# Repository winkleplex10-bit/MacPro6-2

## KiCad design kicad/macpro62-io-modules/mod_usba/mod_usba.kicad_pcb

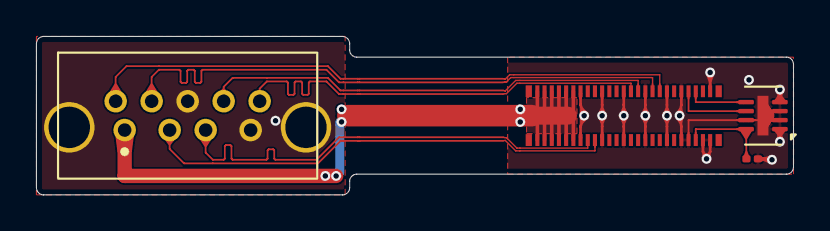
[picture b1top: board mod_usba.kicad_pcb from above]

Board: 2 copper layers, 42.1 x 8.8 mm, 4 parts (0 on the bottom side), 11 nets.

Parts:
C1: 100nF 0201 X5R 10V (3V3_MOD); C_0201_0603Metric
J1: MOD-A - Hong Cheng HC-USB3.0-L137-WJ (C7501870) T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; MP62_MOD_USB_A3_HC-USB3.0-L137-WJ
J2: DF40C-50DP-0.4V(51) C424645 -> JMn DF40C-50DS (PM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; MP62_Hirose_DF40C-50DP-0.4V
U1: BL24C02F-NTRC (C2828222) 24C02 ID EEPROM @0x50; DFN-8-1EP_2x3mm_P0.5mm_EP0.61x2.2mm

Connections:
3V3_MOD: C1.1, J2.46, U1.8
D_N: J1.2, J2.18
D_P: J1.3, J2.16
GND: C1.2, J1.4, J1.7, J1.S, J2.13, J2.14, J2.19, J2.20, J2.25, J2.26, J2.31, J2.32, J2.37, J2.38, J2.41, J2.42, J2.44, J2.48, J2.49, J2.50, U1.1, U1.2, U1.3, U1.4, U1.7, U1.9
ID_SCL: J2.43, U1.6
ID_SDA: J2.45, U1.5
SSRX_N: J1.5, J2.27
SSRX_P: J1.6, J2.29
SSTX_N: J1.8, J2.33
SSTX_P: J1.9, J2.35
VBUS: J1.1, J2.1, J2.2, J2.3, J2.4, J2.5, J2.6, J2.7, J2.8, J2.9, J2.10, J2.11, J2.12

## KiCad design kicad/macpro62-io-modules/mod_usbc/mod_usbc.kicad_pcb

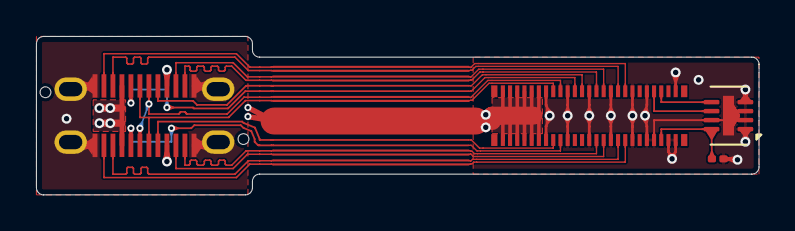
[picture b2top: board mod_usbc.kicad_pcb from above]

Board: 2 copper layers, 40.1 x 8.8 mm, 4 parts (0 on the bottom side), 19 nets.

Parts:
C1: 100nF 0201 X5R 10V (3V3_MOD); C_0201_0603Metric
J1: MOD-C - HOAUC HYCW417-USBC24-180B (C5342202) SMD 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; HOAUC_HYCW417-USBC24-180B
J2: DF40C-50DP-0.4V(51) C424645 -> JMn DF40C-50DS (PM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; MP62_Hirose_DF40C-50DP-0.4V
U1: BL24C02F-NTRC (C2828222) 24C02 ID EEPROM @0x50; DFN-8-1EP_2x3mm_P0.5mm_EP0.61x2.2mm

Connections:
3V3_MOD: C1.1, J2.46, U1.8
CC1: J1.A5, J2.21
CC2: J1.B5, J2.16
D_N: J1.A7, J1.B7, J2.17
D_P: J1.A6, J1.B6, J2.15
GND: C1.2, J1.A1, J1.A12, J1.B1, J1.B12, J1.S, J2.13, J2.14, J2.19, J2.20, J2.25, J2.26, J2.31, J2.32, J2.37, J2.38, J2.41, J2.42, J2.44, J2.48, J2.49, J2.50, U1.1, U1.2, U1.3, U1.4, U1.7, U1.9
ID_SCL: J2.43, U1.6
ID_SDA: J2.45, U1.5
SBU1: J1.A8, J2.23
SBU2: J1.B8, J2.18
SSRX1_N: J1.B10, J2.34
SSRX1_P: J1.B11, J2.36
SSRX2_N: J1.A10, J2.29
SSRX2_P: J1.A11, J2.27
SSTX1_N: J1.A3, J2.33
SSTX1_P: J1.A2, J2.35
SSTX2_N: J1.B3, J2.30
SSTX2_P: J1.B2, J2.28
VBUS: J1.A4, J1.A9, J1.B4, J1.B9, J2.1, J2.2, J2.3, J2.4, J2.5, J2.6, J2.7, J2.8, J2.9, J2.10, J2.11, J2.12

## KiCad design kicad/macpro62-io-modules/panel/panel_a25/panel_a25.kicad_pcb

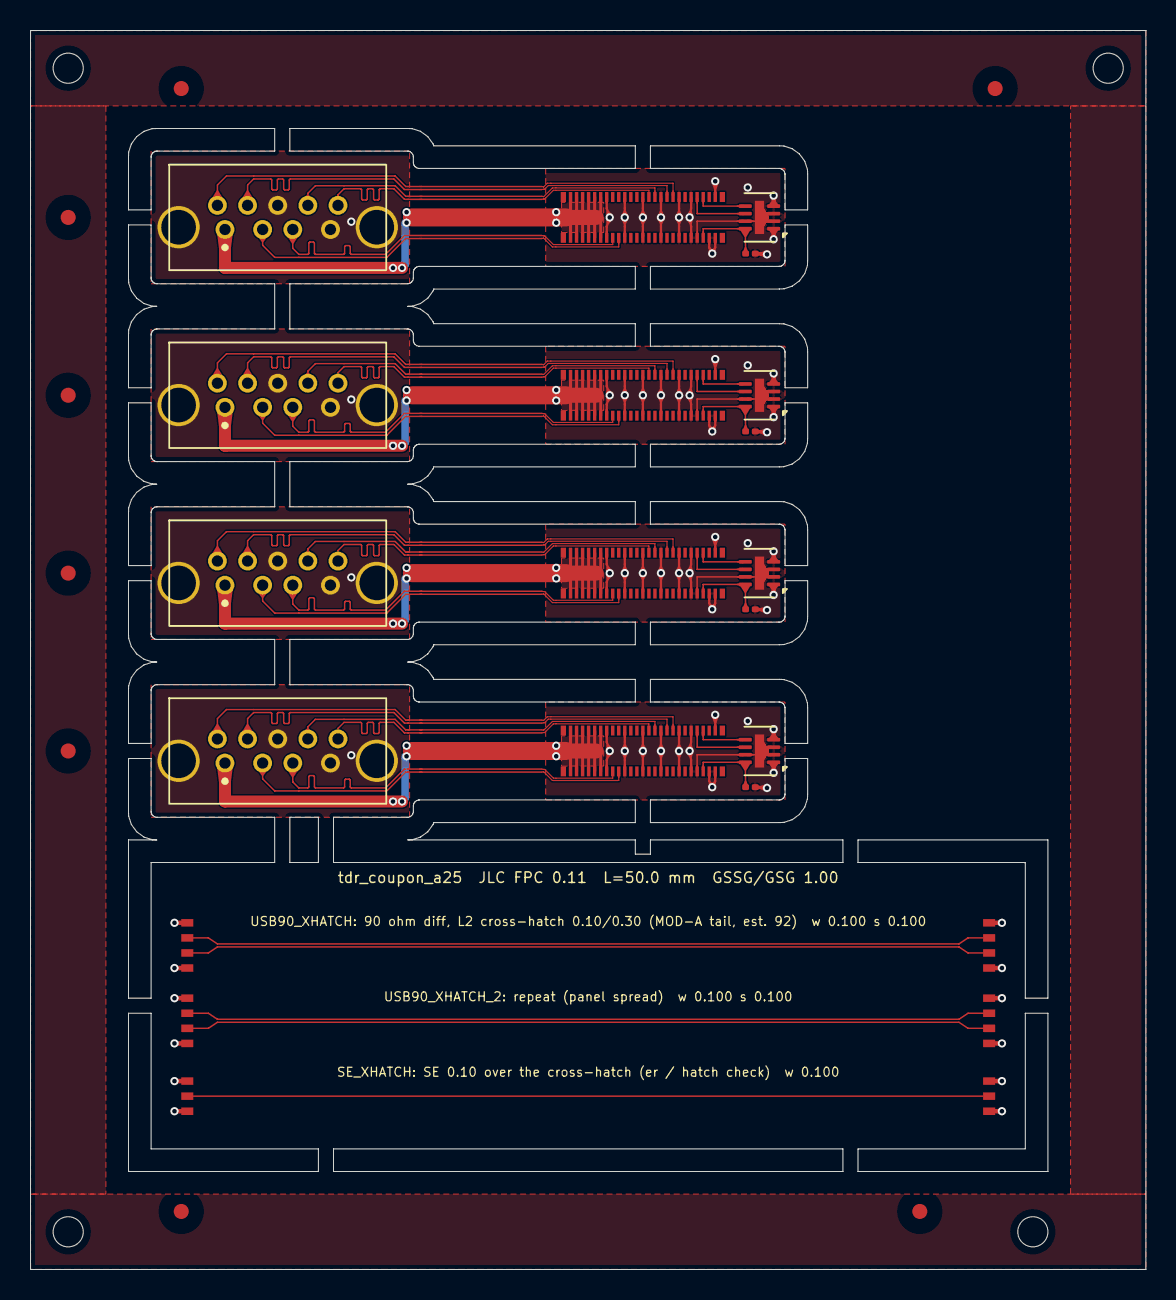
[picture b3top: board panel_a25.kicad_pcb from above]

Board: 2 copper layers, 74.0 x 82.2 mm, 34 parts (0 on the bottom side), 50 nets.

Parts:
C1_A1, C1_A2, C1_A3, C1_A4: 100nF 0201 X5R 10V (3V3_MOD); C_0201_0603Metric
FID1, FID2, FID3, FID4, FID5, FID6, FID7, FID8: Fiducial_1mm_Mask2mm
J1_A1, J1_A2, J1_A3, J1_A4: MOD-A - Hong Cheng HC-USB3.0-L137-WJ (C7501870) T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; MP62_MOD_USB_A3_HC-USB3.0-L137-WJ
J2_A1, J2_A2, J2_A3, J2_A4: DF40C-50DP-0.4V(51) C424645 -> JMn DF40C-50DS (PM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; MP62_Hirose_DF40C-50DP-0.4V
TH1, TH2, TH3, TH4: TOOLING_2.0
TP1A_T, TP1B_T, TP2A_T, TP2B_T, TP3A_T, TP3B_T: TDR_LAUNCH
U1_A1, U1_A2, U1_A3, U1_A4: BL24C02F-NTRC (C2828222) 24C02 ID EEPROM @0x50; DFN-8-1EP_2x3mm_P0.5mm_EP0.61x2.2mm

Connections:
A1/3V3_MOD: C1_A1.1, J2_A1.46, U1_A1.8
A1/D_N: J1_A1.2, J2_A1.18
A1/D_P: J1_A1.3, J2_A1.16
A1/GND: C1_A1.2, J1_A1.4, J1_A1.7, J1_A1.S, J2_A1.13, J2_A1.14, J2_A1.19, J2_A1.20, J2_A1.25, J2_A1.26, J2_A1.31, J2_A1.32, J2_A1.37, J2_A1.38, J2_A1.41, J2_A1.42, J2_A1.44, J2_A1.48, J2_A1.49, J2_A1.50, U1_A1.1, U1_A1.2, U1_A1.3, U1_A1.4, U1_A1.7, U1_A1.9
A1/ID_SCL: J2_A1.43, U1_A1.6
A1/ID_SDA: J2_A1.45, U1_A1.5
A1/SSRX_N: J1_A1.5, J2_A1.27
A1/SSRX_P: J1_A1.6, J2_A1.29
A1/SSTX_N: J1_A1.8, J2_A1.33
A1/SSTX_P: J1_A1.9, J2_A1.35
A1/VBUS: J1_A1.1, J2_A1.1, J2_A1.2, J2_A1.3, J2_A1.4, J2_A1.5, J2_A1.6, J2_A1.7, J2_A1.8, J2_A1.9, J2_A1.10, J2_A1.11, J2_A1.12
A2/3V3_MOD: C1_A2.1, J2_A2.46, U1_A2.8
A2/D_N: J1_A2.2, J2_A2.18
A2/D_P: J1_A2.3, J2_A2.16
A2/GND: C1_A2.2, J1_A2.4, J1_A2.7, J1_A2.S, J2_A2.13, J2_A2.14, J2_A2.19, J2_A2.20, J2_A2.25, J2_A2.26, J2_A2.31, J2_A2.32, J2_A2.37, J2_A2.38, J2_A2.41, J2_A2.42, J2_A2.44, J2_A2.48, J2_A2.49, J2_A2.50, U1_A2.1, U1_A2.2, U1_A2.3, U1_A2.4, U1_A2.7, U1_A2.9
A2/ID_SCL: J2_A2.43, U1_A2.6
A2/ID_SDA: J2_A2.45, U1_A2.5
A2/SSRX_N: J1_A2.5, J2_A2.27
A2/SSRX_P: J1_A2.6, J2_A2.29
A2/SSTX_N: J1_A2.8, J2_A2.33
A2/SSTX_P: J1_A2.9, J2_A2.35
A2/VBUS: J1_A2.1, J2_A2.1, J2_A2.2, J2_A2.3, J2_A2.4, J2_A2.5, J2_A2.6, J2_A2.7, J2_A2.8, J2_A2.9, J2_A2.10, J2_A2.11, J2_A2.12
A3/3V3_MOD: C1_A3.1, J2_A3.46, U1_A3.8
A3/D_N: J1_A3.2, J2_A3.18
A3/D_P: J1_A3.3, J2_A3.16
A3/GND: C1_A3.2, J1_A3.4, J1_A3.7, J1_A3.S, J2_A3.13, J2_A3.14, J2_A3.19, J2_A3.20, J2_A3.25, J2_A3.26, J2_A3.31, J2_A3.32, J2_A3.37, J2_A3.38, J2_A3.41, J2_A3.42, J2_A3.44, J2_A3.48, J2_A3.49, J2_A3.50, U1_A3.1, U1_A3.2, U1_A3.3, U1_A3.4, U1_A3.7, U1_A3.9
A3/ID_SCL: J2_A3.43, U1_A3.6
A3/ID_SDA: J2_A3.45, U1_A3.5
A3/SSRX_N: J1_A3.5, J2_A3.27
A3/SSRX_P: J1_A3.6, J2_A3.29
A3/SSTX_N: J1_A3.8, J2_A3.33
A3/SSTX_P: J1_A3.9, J2_A3.35
A3/VBUS: J1_A3.1, J2_A3.1, J2_A3.2, J2_A3.3, J2_A3.4, J2_A3.5, J2_A3.6, J2_A3.7, J2_A3.8, J2_A3.9, J2_A3.10, J2_A3.11, J2_A3.12
A4/3V3_MOD: C1_A4.1, J2_A4.46, U1_A4.8
A4/D_N: J1_A4.2, J2_A4.18
A4/D_P: J1_A4.3, J2_A4.16
A4/GND: C1_A4.2, J1_A4.4, J1_A4.7, J1_A4.S, J2_A4.13, J2_A4.14, J2_A4.19, J2_A4.20, J2_A4.25, J2_A4.26, J2_A4.31, J2_A4.32, J2_A4.37, J2_A4.38, J2_A4.41, J2_A4.42, J2_A4.44, J2_A4.48, J2_A4.49, J2_A4.50, U1_A4.1, U1_A4.2, U1_A4.3, U1_A4.4, U1_A4.7, U1_A4.9
A4/ID_SCL: J2_A4.43, U1_A4.6
A4/ID_SDA: J2_A4.45, U1_A4.5
A4/SSRX_N: J1_A4.5, J2_A4.27
A4/SSRX_P: J1_A4.6, J2_A4.29
A4/SSTX_N: J1_A4.8, J2_A4.33
A4/SSTX_P: J1_A4.9, J2_A4.35
A4/VBUS: J1_A4.1, J2_A4.1, J2_A4.2, J2_A4.3, J2_A4.4, J2_A4.5, J2_A4.6, J2_A4.7, J2_A4.8, J2_A4.9, J2_A4.10, J2_A4.11, J2_A4.12
T/GND: TP1A_T.1, TP1A_T.4, TP1B_T.1, TP1B_T.4, TP2A_T.1, TP2A_T.4, TP2B_T.1, TP2B_T.4, TP3A_T.1, TP3A_T.3, TP3B_T.1, TP3B_T.3
T/SE_XHATCH: TP3A_T.2, TP3B_T.2
T/USB90_XHATCH_2_N: TP2A_T.3, TP2B_T.3
T/USB90_XHATCH_2_P: TP2A_T.2, TP2B_T.2
T/USB90_XHATCH_N: TP1A_T.3, TP1B_T.3
T/USB90_XHATCH_P: TP1A_T.2, TP1B_T.2

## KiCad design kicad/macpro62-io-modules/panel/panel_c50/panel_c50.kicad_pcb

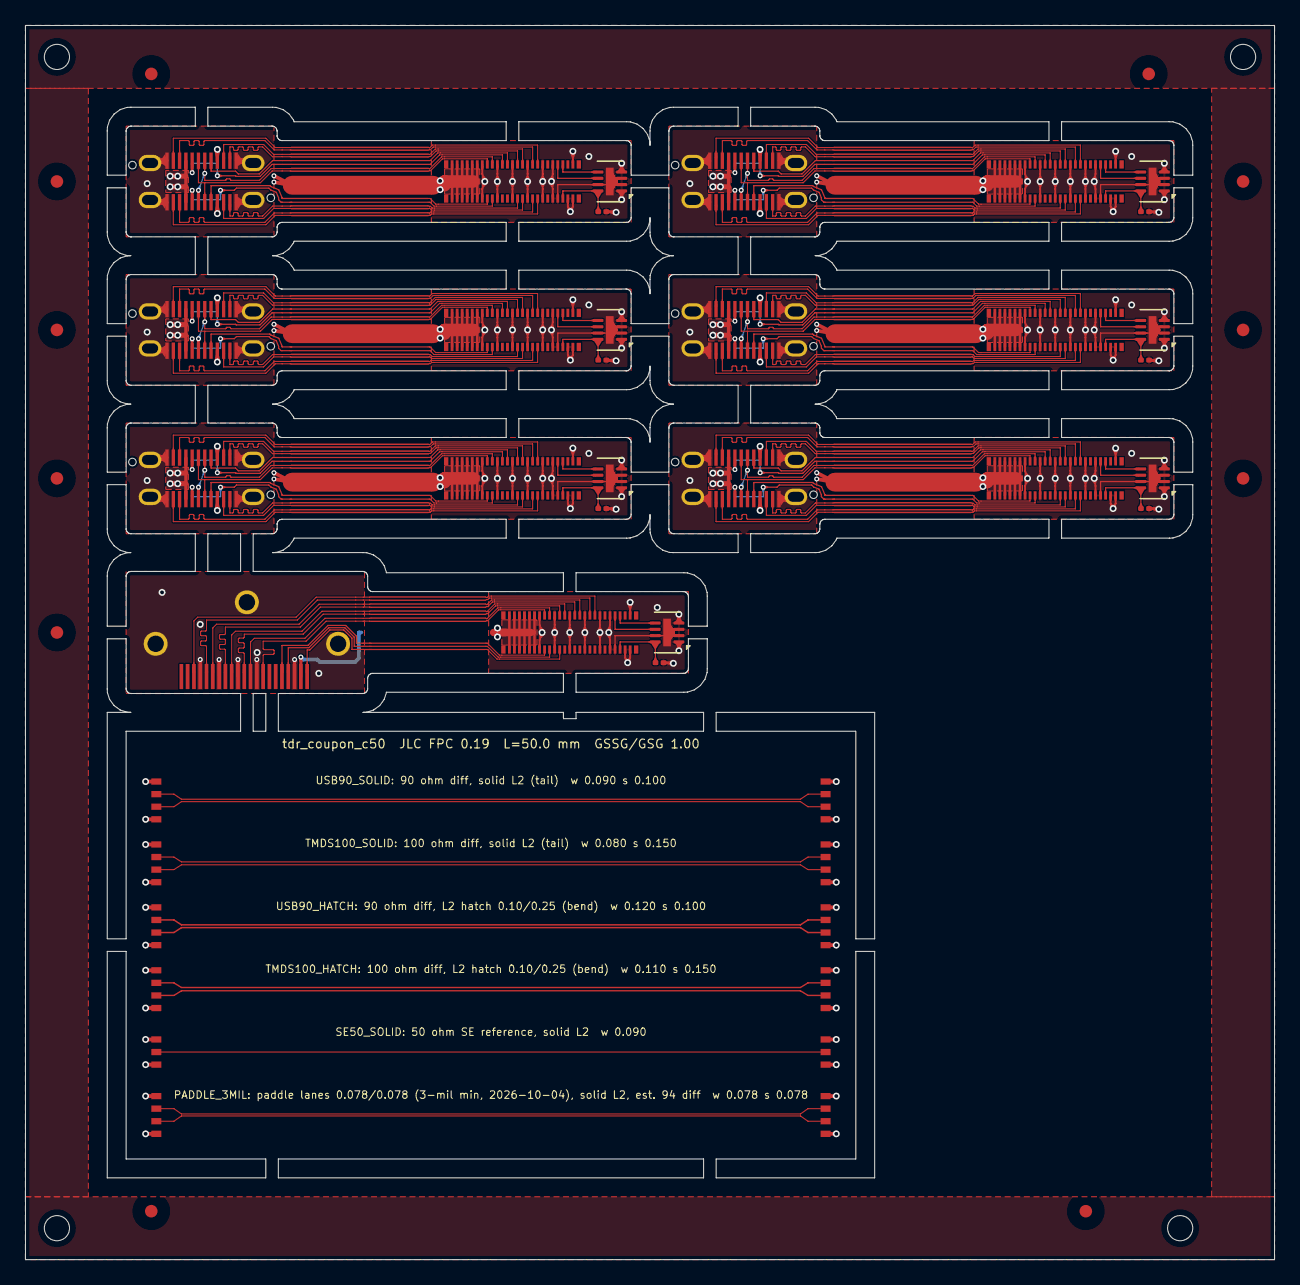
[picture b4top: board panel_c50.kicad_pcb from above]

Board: 2 copper layers, 99.3 x 98.1 mm, 55 parts (0 on the bottom side), 142 nets.

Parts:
C1_C1, C1_C2, C1_C3, C1_C4, C1_C5, C1_C6, C1_H: 100nF 0201 X5R 10V (3V3_MOD); C_0201_0603Metric
FID1, FID2, FID3, FID4, FID5, FID6, FID7, FID8, FID9, FID10, FID11: Fiducial_1mm_Mask2mm
J1_C1, J1_C2, J1_C3, J1_C4, J1_C5, J1_C6: MOD-C - HOAUC HYCW417-USBC24-180B (C5342202) SMD 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; HOAUC_HYCW417-USBC24-180B
J1_H: MOD-H - HOAUC HYC79-HDMIA19-105 (C711353) 19 SMD 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; HOAUC_HYC79-HDMIA19-105
J2_C1, J2_C2, J2_C3, J2_C4, J2_C5, J2_C6, J2_H: DF40C-50DP-0.4V(51) C424645 -> JMn DF40C-50DS (PM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; MP62_Hirose_DF40C-50DP-0.4V
TH1, TH2, TH3, TH4: TOOLING_2.0
TP1A_T, TP1B_T, TP2A_T, TP2B_T, TP3A_T, TP3B_T, TP4A_T, TP4B_T, TP5A_T, TP5B_T, TP6A_T, TP6B_T: TDR_LAUNCH
U1_C1, U1_C2, U1_C3, U1_C4, U1_C5, U1_C6, U1_H: BL24C02F-NTRC (C2828222) 24C02 ID EEPROM @0x50; DFN-8-1EP_2x3mm_P0.5mm_EP0.61x2.2mm

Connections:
C1/3V3_MOD: C1_C1.1, J2_C1.46, U1_C1.8
C1/CC1: J1_C1.A5, J2_C1.21
C1/CC2: J1_C1.B5, J2_C1.16
C1/D_N: J1_C1.A7, J1_C1.B7, J2_C1.17
C1/D_P: J1_C1.A6, J1_C1.B6, J2_C1.15
C1/GND: C1_C1.2, J1_C1.A1, J1_C1.A12, J1_C1.B1, J1_C1.B12, J1_C1.S, J2_C1.13, J2_C1.14, J2_C1.19, J2_C1.20, J2_C1.25, J2_C1.26, J2_C1.31, J2_C1.32, J2_C1.37, J2_C1.38, J2_C1.41, J2_C1.42, J2_C1.44, J2_C1.48, J2_C1.49, J2_C1.50, U1_C1.1, U1_C1.2, U1_C1.3, U1_C1.4, U1_C1.7, U1_C1.9
C1/ID_SCL: J2_C1.43, U1_C1.6
C1/ID_SDA: J2_C1.45, U1_C1.5
C1/SBU1: J1_C1.A8, J2_C1.23
C1/SBU2: J1_C1.B8, J2_C1.18
C1/SSRX1_N: J1_C1.B10, J2_C1.34
C1/SSRX1_P: J1_C1.B11, J2_C1.36
C1/SSRX2_N: J1_C1.A10, J2_C1.29
C1/SSRX2_P: J1_C1.A11, J2_C1.27
C1/SSTX1_N: J1_C1.A3, J2_C1.33
C1/SSTX1_P: J1_C1.A2, J2_C1.35
C1/SSTX2_N: J1_C1.B3, J2_C1.30
C1/SSTX2_P: J1_C1.B2, J2_C1.28
C1/VBUS: J1_C1.A4, J1_C1.A9, J1_C1.B4, J1_C1.B9, J2_C1.1, J2_C1.2, J2_C1.3, J2_C1.4, J2_C1.5, J2_C1.6, J2_C1.7, J2_C1.8, J2_C1.9, J2_C1.10, J2_C1.11, J2_C1.12
C2/3V3_MOD: C1_C2.1, J2_C2.46, U1_C2.8
C2/CC1: J1_C2.A5, J2_C2.21
C2/CC2: J1_C2.B5, J2_C2.16
C2/D_N: J1_C2.A7, J1_C2.B7, J2_C2.17
C2/D_P: J1_C2.A6, J1_C2.B6, J2_C2.15
C2/GND: C1_C2.2, J1_C2.A1, J1_C2.A12, J1_C2.B1, J1_C2.B12, J1_C2.S, J2_C2.13, J2_C2.14, J2_C2.19, J2_C2.20, J2_C2.25, J2_C2.26, J2_C2.31, J2_C2.32, J2_C2.37, J2_C2.38, J2_C2.41, J2_C2.42, J2_C2.44, J2_C2.48, J2_C2.49, J2_C2.50, U1_C2.1, U1_C2.2, U1_C2.3, U1_C2.4, U1_C2.7, U1_C2.9
C2/ID_SCL: J2_C2.43, U1_C2.6
C2/ID_SDA: J2_C2.45, U1_C2.5
C2/SBU1: J1_C2.A8, J2_C2.23
C2/SBU2: J1_C2.B8, J2_C2.18
C2/SSRX1_N: J1_C2.B10, J2_C2.34
C2/SSRX1_P: J1_C2.B11, J2_C2.36
C2/SSRX2_N: J1_C2.A10, J2_C2.29
C2/SSRX2_P: J1_C2.A11, J2_C2.27
C2/SSTX1_N: J1_C2.A3, J2_C2.33
C2/SSTX1_P: J1_C2.A2, J2_C2.35
C2/SSTX2_N: J1_C2.B3, J2_C2.30
C2/SSTX2_P: J1_C2.B2, J2_C2.28
C2/VBUS: J1_C2.A4, J1_C2.A9, J1_C2.B4, J1_C2.B9, J2_C2.1, J2_C2.2, J2_C2.3, J2_C2.4, J2_C2.5, J2_C2.6, J2_C2.7, J2_C2.8, J2_C2.9, J2_C2.10, J2_C2.11, J2_C2.12
C3/3V3_MOD: C1_C3.1, J2_C3.46, U1_C3.8
C3/CC1: J1_C3.A5, J2_C3.21
C3/CC2: J1_C3.B5, J2_C3.16
C3/D_N: J1_C3.A7, J1_C3.B7, J2_C3.17
C3/D_P: J1_C3.A6, J1_C3.B6, J2_C3.15
C3/GND: C1_C3.2, J1_C3.A1, J1_C3.A12, J1_C3.B1, J1_C3.B12, J1_C3.S, J2_C3.13, J2_C3.14, J2_C3.19, J2_C3.20, J2_C3.25, J2_C3.26, J2_C3.31, J2_C3.32, J2_C3.37, J2_C3.38, J2_C3.41, J2_C3.42, J2_C3.44, J2_C3.48, J2_C3.49, J2_C3.50, U1_C3.1, U1_C3.2, U1_C3.3, U1_C3.4, U1_C3.7, U1_C3.9
C3/ID_SCL: J2_C3.43, U1_C3.6
C3/ID_SDA: J2_C3.45, U1_C3.5
C3/SBU1: J1_C3.A8, J2_C3.23
C3/SBU2: J1_C3.B8, J2_C3.18
C3/SSRX1_N: J1_C3.B10, J2_C3.34
C3/SSRX1_P: J1_C3.B11, J2_C3.36
C3/SSRX2_N: J1_C3.A10, J2_C3.29
C3/SSRX2_P: J1_C3.A11, J2_C3.27
C3/SSTX1_N: J1_C3.A3, J2_C3.33
C3/SSTX1_P: J1_C3.A2, J2_C3.35
C3/SSTX2_N: J1_C3.B3, J2_C3.30
C3/SSTX2_P: J1_C3.B2, J2_C3.28
C3/VBUS: J1_C3.A4, J1_C3.A9, J1_C3.B4, J1_C3.B9, J2_C3.1, J2_C3.2, J2_C3.3, J2_C3.4, J2_C3.5, J2_C3.6, J2_C3.7, J2_C3.8, J2_C3.9, J2_C3.10, J2_C3.11, J2_C3.12
C4/3V3_MOD: C1_C4.1, J2_C4.46, U1_C4.8
C4/CC1: J1_C4.A5, J2_C4.21
C4/CC2: J1_C4.B5, J2_C4.16
C4/D_N: J1_C4.A7, J1_C4.B7, J2_C4.17
C4/D_P: J1_C4.A6, J1_C4.B6, J2_C4.15
C4/GND: C1_C4.2, J1_C4.A1, J1_C4.A12, J1_C4.B1, J1_C4.B12, J1_C4.S, J2_C4.13, J2_C4.14, J2_C4.19, J2_C4.20, J2_C4.25, J2_C4.26, J2_C4.31, J2_C4.32, J2_C4.37, J2_C4.38, J2_C4.41, J2_C4.42, J2_C4.44, J2_C4.48, J2_C4.49, J2_C4.50, U1_C4.1, U1_C4.2, U1_C4.3, U1_C4.4, U1_C4.7, U1_C4.9
C4/ID_SCL: J2_C4.43, U1_C4.6
C4/ID_SDA: J2_C4.45, U1_C4.5
C4/SBU1: J1_C4.A8, J2_C4.23
C4/SBU2: J1_C4.B8, J2_C4.18
C4/SSRX1_N: J1_C4.B10, J2_C4.34
C4/SSRX1_P: J1_C4.B11, J2_C4.36
C4/SSRX2_N: J1_C4.A10, J2_C4.29
C4/SSRX2_P: J1_C4.A11, J2_C4.27
C4/SSTX1_N: J1_C4.A3, J2_C4.33
C4/SSTX1_P: J1_C4.A2, J2_C4.35
C4/SSTX2_N: J1_C4.B3, J2_C4.30
C4/SSTX2_P: J1_C4.B2, J2_C4.28
C4/VBUS: J1_C4.A4, J1_C4.A9, J1_C4.B4, J1_C4.B9, J2_C4.1, J2_C4.2, J2_C4.3, J2_C4.4, J2_C4.5, J2_C4.6, J2_C4.7, J2_C4.8, J2_C4.9, J2_C4.10, J2_C4.11, J2_C4.12
C5/3V3_MOD: C1_C5.1, J2_C5.46, U1_C5.8
C5/CC1: J1_C5.A5, J2_C5.21
C5/CC2: J1_C5.B5, J2_C5.16
C5/D_N: J1_C5.A7, J1_C5.B7, J2_C5.17
C5/D_P: J1_C5.A6, J1_C5.B6, J2_C5.15
C5/GND: C1_C5.2, J1_C5.A1, J1_C5.A12, J1_C5.B1, J1_C5.B12, J1_C5.S, J2_C5.13, J2_C5.14, J2_C5.19, J2_C5.20, J2_C5.25, J2_C5.26, J2_C5.31, J2_C5.32, J2_C5.37, J2_C5.38, J2_C5.41, J2_C5.42, J2_C5.44, J2_C5.48, J2_C5.49, J2_C5.50, U1_C5.1, U1_C5.2, U1_C5.3, U1_C5.4, U1_C5.7, U1_C5.9
C5/ID_SCL: J2_C5.43, U1_C5.6
C5/ID_SDA: J2_C5.45, U1_C5.5
C5/SBU1: J1_C5.A8, J2_C5.23
C5/SBU2: J1_C5.B8, J2_C5.18
C5/SSRX1_N: J1_C5.B10, J2_C5.34
C5/SSRX1_P: J1_C5.B11, J2_C5.36
C5/SSRX2_N: J1_C5.A10, J2_C5.29
C5/SSRX2_P: J1_C5.A11, J2_C5.27
C5/SSTX1_N: J1_C5.A3, J2_C5.33
C5/SSTX1_P: J1_C5.A2, J2_C5.35
C5/SSTX2_N: J1_C5.B3, J2_C5.30
C5/SSTX2_P: J1_C5.B2, J2_C5.28
C5/VBUS: J1_C5.A4, J1_C5.A9, J1_C5.B4, J1_C5.B9, J2_C5.1, J2_C5.2, J2_C5.3, J2_C5.4, J2_C5.5, J2_C5.6, J2_C5.7, J2_C5.8, J2_C5.9, J2_C5.10, J2_C5.11, J2_C5.12
C6/3V3_MOD: C1_C6.1, J2_C6.46, U1_C6.8
C6/CC1: J1_C6.A5, J2_C6.21
C6/CC2: J1_C6.B5, J2_C6.16
C6/D_N: J1_C6.A7, J1_C6.B7, J2_C6.17
C6/D_P: J1_C6.A6, J1_C6.B6, J2_C6.15
C6/GND: C1_C6.2, J1_C6.A1, J1_C6.A12, J1_C6.B1, J1_C6.B12, J1_C6.S, J2_C6.13, J2_C6.14, J2_C6.19, J2_C6.20, J2_C6.25, J2_C6.26, J2_C6.31, J2_C6.32, J2_C6.37, J2_C6.38, J2_C6.41, J2_C6.42, J2_C6.44, J2_C6.48, J2_C6.49, J2_C6.50, U1_C6.1, U1_C6.2, U1_C6.3, U1_C6.4, U1_C6.7, U1_C6.9
C6/ID_SCL: J2_C6.43, U1_C6.6
C6/ID_SDA: J2_C6.45, U1_C6.5
C6/SBU1: J1_C6.A8, J2_C6.23
C6/SBU2: J1_C6.B8, J2_C6.18
C6/SSRX1_N: J1_C6.B10, J2_C6.34
C6/SSRX1_P: J1_C6.B11, J2_C6.36
C6/SSRX2_N: J1_C6.A10, J2_C6.29
C6/SSRX2_P: J1_C6.A11, J2_C6.27
C6/SSTX1_N: J1_C6.A3, J2_C6.33
C6/SSTX1_P: J1_C6.A2, J2_C6.35
C6/SSTX2_N: J1_C6.B3, J2_C6.30
C6/SSTX2_P: J1_C6.B2, J2_C6.28
C6/VBUS: J1_C6.A4, J1_C6.A9, J1_C6.B4, J1_C6.B9, J2_C6.1, J2_C6.2, J2_C6.3, J2_C6.4, J2_C6.5, J2_C6.6, J2_C6.7, J2_C6.8, J2_C6.9, J2_C6.10, J2_C6.11, J2_C6.12
H/3V3_MOD: C1_H.1, J2_H.46, U1_H.8
H/CK_N: J1_H.12, J2_H.15
H/CK_P: J1_H.10, J2_H.17
H/D0_N: J1_H.9, J2_H.21
H/D0_P: J1_H.7, J2_H.23
H/D1_N: J1_H.6, J2_H.27
H/D1_P: J1_H.4, J2_H.29
H/D2_N: J1_H.3, J2_H.33
H/D2_P: J1_H.1, J2_H.35
H/DDC_SCL: J1_H.15, J2_H.16
H/DDC_SDA: J1_H.16, J2_H.18
H/GND: C1_H.2, J1_H.2, J1_H.5, J1_H.8, J1_H.11, J1_H.17, J1_H.S, J2_H.13, J2_H.14, J2_H.19, J2_H.20, J2_H.25, J2_H.26, J2_H.31, J2_H.32, J2_H.37, J2_H.38, J2_H.41, J2_H.42, J2_H.44, J2_H.48, J2_H.49, J2_H.50, U1_H.1, U1_H.2, U1_H.3, U1_H.4, U1_H.7, U1_H.9
H/HPD: J1_H.19, J2_H.22
H/ID_SCL: J2_H.43, U1_H.6
H/ID_SDA: J2_H.45, U1_H.5
H/VBUS: J1_H.18, J2_H.1, J2_H.2, J2_H.3, J2_H.4, J2_H.5, J2_H.6, J2_H.7, J2_H.8, J2_H.9, J2_H.10, J2_H.11, J2_H.12
T/GND: TP1A_T.1, TP1A_T.4, TP1B_T.1, TP1B_T.4, TP2A_T.1, TP2A_T.4, TP2B_T.1, TP2B_T.4, TP3A_T.1, TP3A_T.4, TP3B_T.1, TP3B_T.4, TP4A_T.1, TP4A_T.4, TP4B_T.1, TP4B_T.4, TP5A_T.1, TP5A_T.3, TP5B_T.1, TP5B_T.3, TP6A_T.1, TP6A_T.4, TP6B_T.1, TP6B_T.4
T/PADDLE_3MIL_N: TP6A_T.3, TP6B_T.3
T/PADDLE_3MIL_P: TP6A_T.2, TP6B_T.2
T/SE50_SOLID: TP5A_T.2, TP5B_T.2
T/TMDS100_HATCH_N: TP4A_T.3, TP4B_T.3
T/TMDS100_HATCH_P: TP4A_T.2, TP4B_T.2
T/TMDS100_SOLID_N: TP2A_T.3, TP2B_T.3
T/TMDS100_SOLID_P: TP2A_T.2, TP2B_T.2
T/USB90_HATCH_N: TP3A_T.3, TP3B_T.3
T/USB90_HATCH_P: TP3A_T.2, TP3B_T.2
T/USB90_SOLID_N: TP1A_T.3, TP1B_T.3
T/USB90_SOLID_P: TP1A_T.2, TP1B_T.2

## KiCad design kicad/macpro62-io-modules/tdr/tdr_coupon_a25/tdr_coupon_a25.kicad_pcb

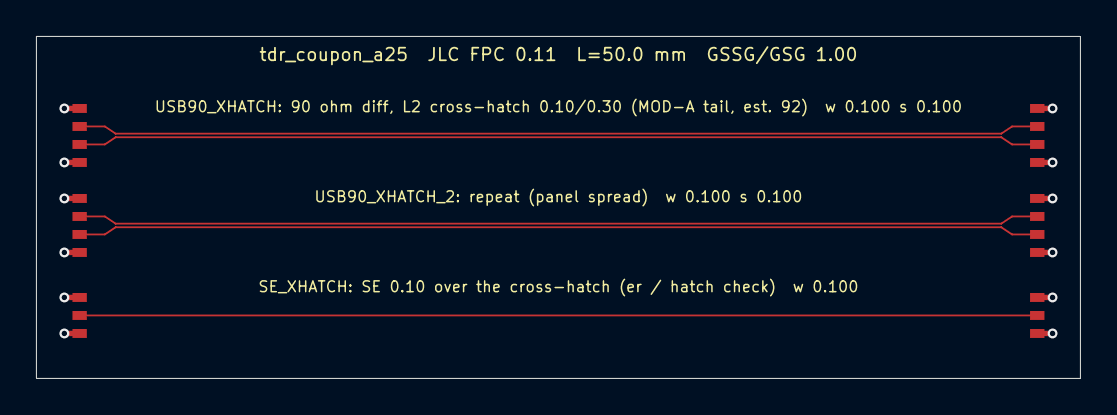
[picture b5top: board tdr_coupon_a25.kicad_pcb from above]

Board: 2 copper layers, 58.0 x 19.0 mm, 6 parts (0 on the bottom side), 6 nets.

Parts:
TP1A, TP1B, TP2A, TP2B, TP3A, TP3B: TDR_LAUNCH

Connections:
GND: TP1A.1, TP1A.4, TP1B.1, TP1B.4, TP2A.1, TP2A.4, TP2B.1, TP2B.4, TP3A.1, TP3A.3, TP3B.1, TP3B.3
SE_XHATCH: TP3A.2, TP3B.2
USB90_XHATCH_2_N: TP2A.3, TP2B.3
USB90_XHATCH_2_P: TP2A.2, TP2B.2
USB90_XHATCH_N: TP1A.3, TP1B.3
USB90_XHATCH_P: TP1A.2, TP1B.2

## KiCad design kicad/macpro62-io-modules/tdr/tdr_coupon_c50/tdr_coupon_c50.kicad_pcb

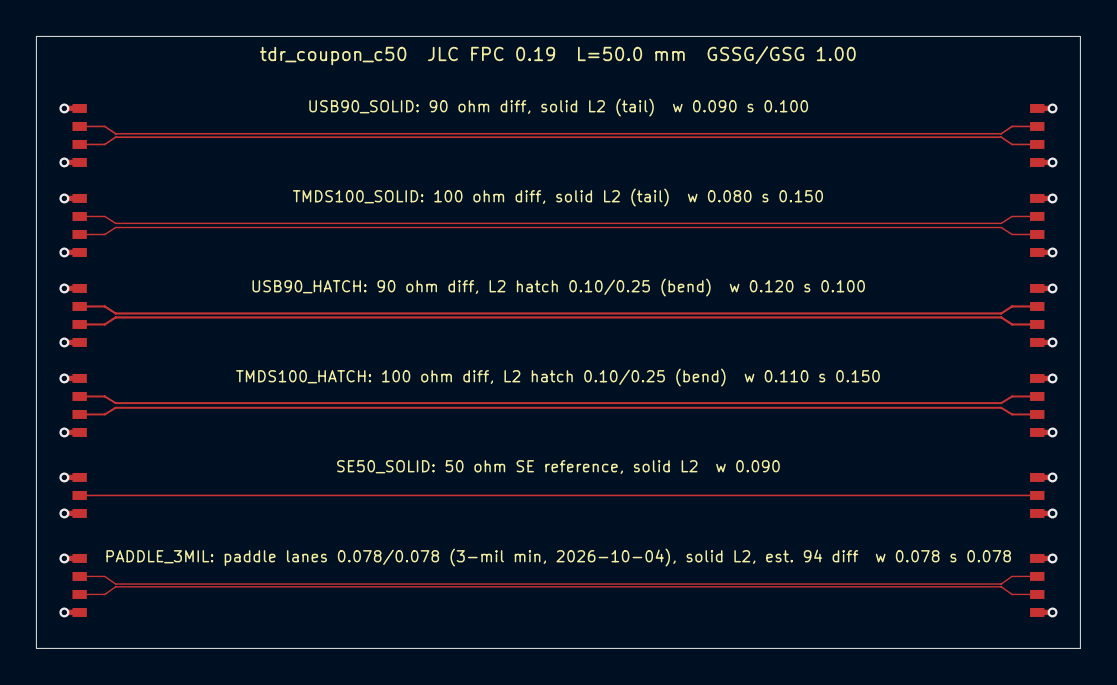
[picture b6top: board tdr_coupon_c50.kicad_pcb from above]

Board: 2 copper layers, 58.0 x 34.0 mm, 12 parts (0 on the bottom side), 12 nets.

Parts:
TP1A, TP1B, TP2A, TP2B, TP3A, TP3B, TP4A, TP4B, TP5A, TP5B, TP6A, TP6B: TDR_LAUNCH

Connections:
GND: TP1A.1, TP1A.4, TP1B.1, TP1B.4, TP2A.1, TP2A.4, TP2B.1, TP2B.4, TP3A.1, TP3A.4, TP3B.1, TP3B.4, TP4A.1, TP4A.4, TP4B.1, TP4B.4, TP5A.1, TP5A.3, TP5B.1, TP5B.3, TP6A.1, TP6A.4, TP6B.1, TP6B.4
PADDLE_3MIL_N: TP6A.3, TP6B.3
PADDLE_3MIL_P: TP6A.2, TP6B.2
SE50_SOLID: TP5A.2, TP5B.2
TMDS100_HATCH_N: TP4A.3, TP4B.3
TMDS100_HATCH_P: TP4A.2, TP4B.2
TMDS100_SOLID_N: TP2A.3, TP2B.3
TMDS100_SOLID_P: TP2A.2, TP2B.2
USB90_HATCH_N: TP3A.3, TP3B.3
USB90_HATCH_P: TP3A.2, TP3B.2
USB90_SOLID_N: TP1A.3, TP1B.3
USB90_SOLID_P: TP1A.2, TP1B.2
